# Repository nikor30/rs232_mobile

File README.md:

# RS232-WLAN-Konsole

Mobiler serieller Konsolenserver auf ESP32-Basis: mit dem WLAN-Hotspot des Geräts verbinden, `http://192.168.4.1` öffnen, Terminal auf Switch, Router oder Firewall. Keine App, kein Treiber, kein USB-Seriell-Adapter — und auf Wunsch aus der Ferne über die Leitstelle.

Firmware-Stand: **v1.8.2** · Board: **Waveshare ESP32-S3-Touch-LCD-2** · Oberflächen auf Englisch, Deutsch und Portugiesisch

## Was es kann

| Wo | Was |
|---|---|
| **Am Gerät** | Touch-Display mit Portstatus, Baudrate, Auto-Baud, BREAK, Terminal und Skripten; Akku mit Ladeanzeige und Sparmodus |
| **Im Browser** | xterm.js-Terminal über den eigenen Hotspot oder das Firmennetz, ohne Installation — am Handy wie am Notebook |
| **Im Netz** | Raw-TCP und Telnet je Port (PuTTY), Bluetooth-LE-Konsole, XMODEM/YMODEM, 802.1X (PEAP, TTLS, EAP-TLS), HTTPS |
| **Auf der SD-Karte** | Mitschnitte je Port, gespeicherte Konfigurationen zum Abspielen, verschlüsselte Sicherung; die Karte lässt sich als USB-Stick verleihen |
| **Aus der Ferne** | Leitstelle mit Geräteübersicht, Fernkonsole Ende-zu-Ende verschlüsselt, Firmware-Updates nur signiert (ML-DSA-65), Images auf die SD-Karte |

<table>
  <tr>
    <td align="center" width="38%"><br><sub>Touch-Display am Gerät</sub></td>
    <td align="center"><br><sub>Weboberfläche des Geräts am Handy</sub></td>
  </tr>
</table>

## Leitstelle

Geräte melden sich ausgehend per HTTPS bei einem Server — kein offener Port am Gerät, kein VPN. Der Kanal darin ist hybrid verschlüsselt (X25519 + ML-KEM-768); angemeldet wird mit einem sechsstelligen Code vom Display. Konten mit Passwort und Authenticator-App, Gruppen mit Rechten, Standorte, eine Bibliothek für Vorlagen, Firmware und Images.

Die **Fernkonsole** braucht einen Tipp am Gerät (oder eine dort gesetzte Frist für unbeaufsichtigten Zugriff), läuft höchstens 60 Minuten und ist Ende-zu-Ende verschlüsselt: Der Server trägt nur Chiffretext, Display und Browser zeigen denselben Code. Skripte lassen sich im Terminal abspielen, Sitzungen in eine Textdatei aufzeichnen.

## Hardware (Entwurf)

Eine Trägerplatine für das Waveshare-Modul mit **vier galvanisch getrennten RS232-Ports auf RJ45** (Cisco-Belegung; je Port Optokoppler, MAX3232E und eigener isolierter Wandler, aus dem Akku schaltbar) und ein druckbares Gehäuse. Entworfen und per KiCad-DRC geprüft, **noch nicht gebaut** — Quellen, Gerber für PCBWay und STL-Dateien im Zweig [`hardware-carrier`](../../tree/hardware-carrier/hardware).

<table>
  <tr>
    <td align="center"><br><sub>Trägerplatine 78 × 107 mm</sub></td>
    <td align="center"><br><sub>Körper, Platine, Boden</sub></td>
  </tr>
</table>

Heute läuft das Gerät mit einem MAX3232-Modul an einem Port, geprüft an Cisco C3750-X und C2960CX.

## Aufbau

- [`HANDOVER.md`](HANDOVER.md) — Projektstand, Erfahrungswissen, offene Punkte
- [`firmware/`](firmware/) — PlatformIO-Projekt für das Waveshare ESP32-S3-Touch-LCD-2 ([Weboberfläche und Netz](firmware/README.md), [Board](firmware/WAVESHARE.md))
- [`server/`](server/) — Leitstelle (Command-and-Control-Server) in Go: [Konzept](server/KONZEPT.md), [Betrieb und Admin-API](server/README.md)
- [`tests/`](tests/) — Host-Unittests der Firmware und Protokolltests gegen den Server

```bash
cd firmware
pio run -t upload                          # Englisch
pio run -e waveshare-s3-lcd2-de -t upload  # Deutsch (-pt: Portugiesisch)

cd server
docker compose up -d --build               # Leitstelle lokal, siehe server/README.md
```

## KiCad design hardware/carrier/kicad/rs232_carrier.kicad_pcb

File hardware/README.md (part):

# Hardware: Trägerplatine mit vier galvanisch getrennten RS232-Ports und Gehäuse

Stand 15. November 2026: Platine **Revision 0.4** (Neuanfang auf Grundlage des 3D-Modells des Herstellers),
Gehäuse **Revision 0.5** (neu aufgebaut nach dem ersten Probedruck).
Entworfen, geroutet, KiCad-DRC ohne elektrische Fehler, Gehäuse rechnerisch gegen das Herstellermodell
geprüft — **Platine nicht gebaut, Gehäuse in dieser Fassung nicht gedruckt.** Vor der Bestellung die Liste
„Vor der Bestellung prüfen“ abarbeiten.

> **Revision 0.3.1 und älter nicht bauen.** Dort waren die beiden Buchsenleisten für das Modul spiegelverkehrt
> belegt: Die Pinbelegung stammte aus einem Foto der Modulrückseite und wurde wie eine Ansicht von oben
> eingetragen. Jedes Signal lag am falschen Pin, VBAT und Masse eingeschlossen. Revision 0.4 nimmt die Lage
> der Stifte aus dem 3D-Modell des Herstellers, und `generate.py` prüft sie bei jedem Lauf dagegen (`HEADER`).

## Was neu ist in Revision 0.4

- **Modul exakt vermessen**: Alle Maße kommen aus dem STEP-Modell von Waveshare (Abschnitt „Das Modul“).
- **Buchsenleisten richtig herum**, Pin 1 liegt 7,60 mm vom antennenseitigen Platinenrand (vorher 7,3 mm geschätzt).
- **TX/RX per Software kreuzen**: Die Lötbrücken sind entfallen. Je Port schalten zwei Halbleiterrelais
  (CPC2330N) die beiden Leitungen an der Buchse um; die Firmware steuert das über GPIO2/4/6/7.
- **Prüfung der Schaltung, Korrekturen**: isolierter Wandler mit 3,3 V statt 5 V Ausgang (der B0505S liefert
  im Leerlauf über 5,5 V, mehr als der MAX3232 verträgt), Ladungspumpen-Kondensatoren 470 nF, Teiler des
  Aufwärtswandlers 270k/36k, BSS138 statt 2N7002 (schaltet mit 3,3 V sicher), TVS-Dioden an jeder Buchse,
  Verpolschutz am Akkuanschluss, zweiter Akkustecker (MX1.25 wie am Modul).
- **Gehäuse neu in echtem CAD** (CadQuery/OpenCascade, STEP und STL), seit dem ersten Probedruck in
  Revision 0.5: Das Displayglas liegt bündig in einer Öffnung der Oberseite auf einem eigenen Rahmen, in dem
  das Modul geklemmt ist; der Boden rastet mit vier Federarmen; am USB-C-Ende **zwei Tasten für RST und
  BOOT, mitgedruckt als Federzungen des Rahmens**. Drei Teile, nichts Loses, kein Teil braucht Stützen. Das alte OpenSCAD-Gehäuse ist entfernt (es war zusätzlich seitenverkehrt).

## Das Modul

Waveshare ESP32-S3-Touch-LCD-2. Der Hersteller stellt ein vollständiges 3D-Modell bereit
(`esp32-s3-touch-lcd-2_20241108.stp`, STEP AP203 aus Creo, 314 Körper, von CATIA V5 und 3DEXPERIENCE direkt
lesbar), dazu Maßzeichnung und Schaltplan. Die Dateien liegen **nicht im Repository** (Herkunft und Lizenz
beim Hersteller); `vendor/README.md` nennt die Adressen. `enclosure/case.py` prüft das Gehäuse gegen dieses
Modell, wenn es in `hardware/vendor/` liegt.

Koordinaten des Herstellermodells: x quer, y längs (USB-C bei −y, Antenne bei +y), z nach oben zur
Displayseite; Glasoberseite z = +3,60, Platine z = −3,60 … −2,00.

| Maß | Wert (mm) |
|---|---|
| Deckglas | 37,10 × 58,80 × 1,10, Ecken R 2,60 |
| Platine | 35,02 × 48,22 × 1,60 |
| Glasüberstand über die Platine | 5,08 an der USB-C-Seite, 5,50 an der Antennenseite, 1,04 je Längsseite |
| Stapel | Glas 1,10, Touchfolie 0,40, LCD 2,10, Acrylplatte 2,00, Platine 1,60 |
| Glasoberseite bis Platinenunterseite | 7,20 |
| Glasoberseite bis Unterkante der Stiftleistenkörper | 9,70 |
| Glasoberseite bis Stiftspitzen | 15,50 |
| Stiftleisten | 2 × 14 Stifte, Raster 2,54, Reihen 30,48 auseinander; Pin 1 und Pin 28 an der Antennenseite, 7,60 vom Platinenrand |
| Abstandsbolzen M2 | vier, 29,00 × 42,20 |
| Sichtfläche des Displays | 30,99 × 41,20 (240 × 320 Bildpunkte) |
| USB-C-Buchse | Schale außen 8,94 × 3,16, Öffnung 8,34 × 2,56, Achse 1,67 unter der Platinenunterseite, Vorderkante 1,18 über dem Platinenrand und 3,90 hinter der Glaskante; ein Steckerblech taucht 4,78 ein |
| Taster RST und BOOT | TS24CA, seitlich betätigt, Gehäuse 4,55 × 2,30 × 1,80; Stößel 2,00 × 1,00, 1,20 vor dem Tastergehäuse, Spitze 0,28 hinter dem Platinenrand, Achse 0,90 unter der Platinenunterseite; Stößel 18,92 auseinander (RST bei x = +9,47, BOOT bei x = −9,45) |

Das Maßblatt `enclosure/out/waveshare_module_dimensions.pdf` zeigt alles in drei Ansichten. Alle Zahlen stehen
in `carrier/generate.py` im Wörterbuch `WS`; Platine und Gehäuse lesen sie von dort.

Aus dem Schaltplan des Herstellers: Stift 14 (VBAT) ist das Akkunetz des Laders, am MX1.25-Stecker ist Pin 1
der Pluspol, der Stift „5V“ ist USB-VBUS. **Das Modul hat nur eine Keramikantenne und keine IPEX-Buchse**;
eine externe Antenne ginge nur mit Umbau am Modul. Das Gehäuse hat deshalb keine SMA-Bohrung mehr.

## Verzeichnis

| Pfad | Inhalt |
|---|---|
| `carrier/generate.py` | **Die Quelle.** Maße des Moduls (`WS`), Schaltplan, Platine, DRC-Regeln, `bom.csv`, `preview.png` |
| `carrier/kigen.py` | Schreiber für KiCad-7-Dateien (Symbole und Footprints eingebettet, auch für die Unterseite) |
| `carrier/route.py` | Eigener Gitter-Autorouter (zwei Lagen, Vias, Bauteile auf beiden Seiten, Masseflächen) |
| `carrier/drc.py` | Zonen füllen, KiCad-DRC, Fertigungsdaten nach `kicad/fab/` |
| `carrier/check_pours.py` | Prüft unabhängig vom DRC, dass jede Massefläche zusammenhängt, und nennt den Ort einer abgetrennten Insel |
| `carrier/kicad/` | KiCad-7-Projekt; `channel.kicad_sch` ist ein Port und viermal eingebunden |
| `carrier/kicad/fab/` | **Gerber und Bohrdaten als ZIP**, Bestückungsdaten, Schaltplan- und Platinen-PDF, DRC-Bericht |
| `enclosure/case.py` | Gehäuse: Körper, Rahmen (mit den beiden Tasten), Boden; STEP, STL, Prüfungen. Braucht CadQuery |
| `enclosure/printcheck.py` | Prüft die druckfertigen Dateien: Was beginnt über dem Bett in der Luft, und was hält es |
| `enclosure/render.py` | Bilder (POV-Ray) und die Schnittzeichnung `out/detail_sections.png` |
| `enclosure/module_sheet.py` | Maßblatt des Moduls |
| `enclosure/out/` | `body`, `frame`, `base` als STEP und STL, `print/` mit den Teilen in Drucklage, `rs232_console_assembly.step`, Bilder |
| `vendor/` | Hinweis, woher das Herstellermodell kommt (die Dateien selbst nicht) |
| `hat/` | **Zwei-Port-Prototyp** „RS232 CONSOLE HAT v3.0“: Fertigungsdaten, `board.py`, Beschreibung des Gehäuses dazu (`hat/README.md`) |
| `enclosure/out_hat/` | Gehäuse für den Zwei-Port-Prototyp (`case.py --hat`): dieselben Dateien |

Neu erzeugen (KiCad 7, POV-Ray und `pip install cadquery`):

```bash
cd hardware/carrier && python3 generate.py && python3 route.py && python3 drc.py && python3 check_pours.py
cd ../enclosure && python3 case.py && python3 render.py && python3 module_sheet.py
```

`generate.py` ist deterministisch. Änderungen gehören dorthin, nicht in die KiCad-Dateien. Immer in dieser
Reihenfolge laufen lassen und nie zwei Läufe zugleich: `route.py` hängt seine Bahnen an die Platinendatei an.

Der Router ist seit diesem Stand wiederholbar (gleiche Eingabe, gleiches Ergebnis). Drei Masseanschlüsse
bekommen keine eigene Bahn und hängen nur an der Massefläche (`route.py` meldet „left to the pour“). Ob die
Fläche sie wirklich erreicht, entscheidet erst die Füllung in KiCad; `drc.py` und `check_pours.py` prüfen das.
Meldet eines der beiden nach einer Änderung an der Platzierung eine offene Verbindung, hilft ein anderer
Startwert: `ROUTE_SEED=2 python3 route.py`.

## Pinbelegung am Modul

| Port | RX (ESP-Eingang) | TX (ESP-Ausgang) | Versorgung an | Kreuzen |
|---|---|---|---|---|
| 1 | GPIO44 | GPIO21 | GPIO16 | GPIO2 |
| 2 | GPIO15 | GPIO13 | GPIO17 | GPIO4 |
| 3 | GPIO11 | GPIO12 | GPIO18 | GPIO6 |
| 4 | GPIO14 | GPIO9 | GPIO10 | GPIO7 |

GPIO2/4/6/7 gehören am Modul zum Kamerastecker und sind ohne Kamera frei. GPIO43 (U0TXD) bleibt frei, weil
das ROM beim Reset dort schreibt; er liegt mit 3V3, Masse, I²C (GPIO47/48), GPIO8 und VBUS an Stecker J3.
Das Häkchen „RX/TX am Pegelwandler tauschen“ der Firmware darf mit dieser Platine nicht gesetzt werden
(die Optokoppler haben eine feste Richtung).

## Signalweg eines Ports

```
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
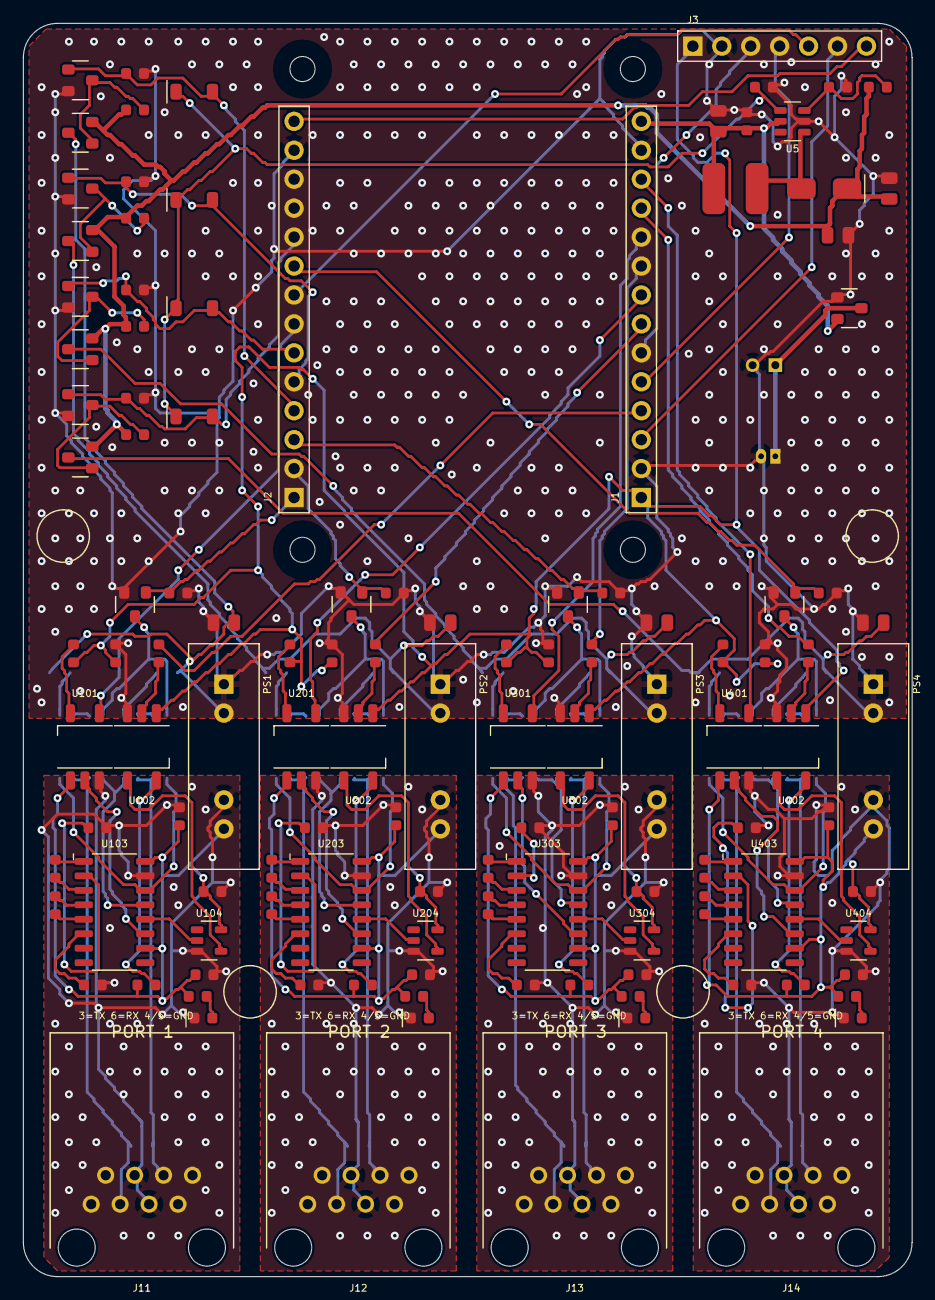
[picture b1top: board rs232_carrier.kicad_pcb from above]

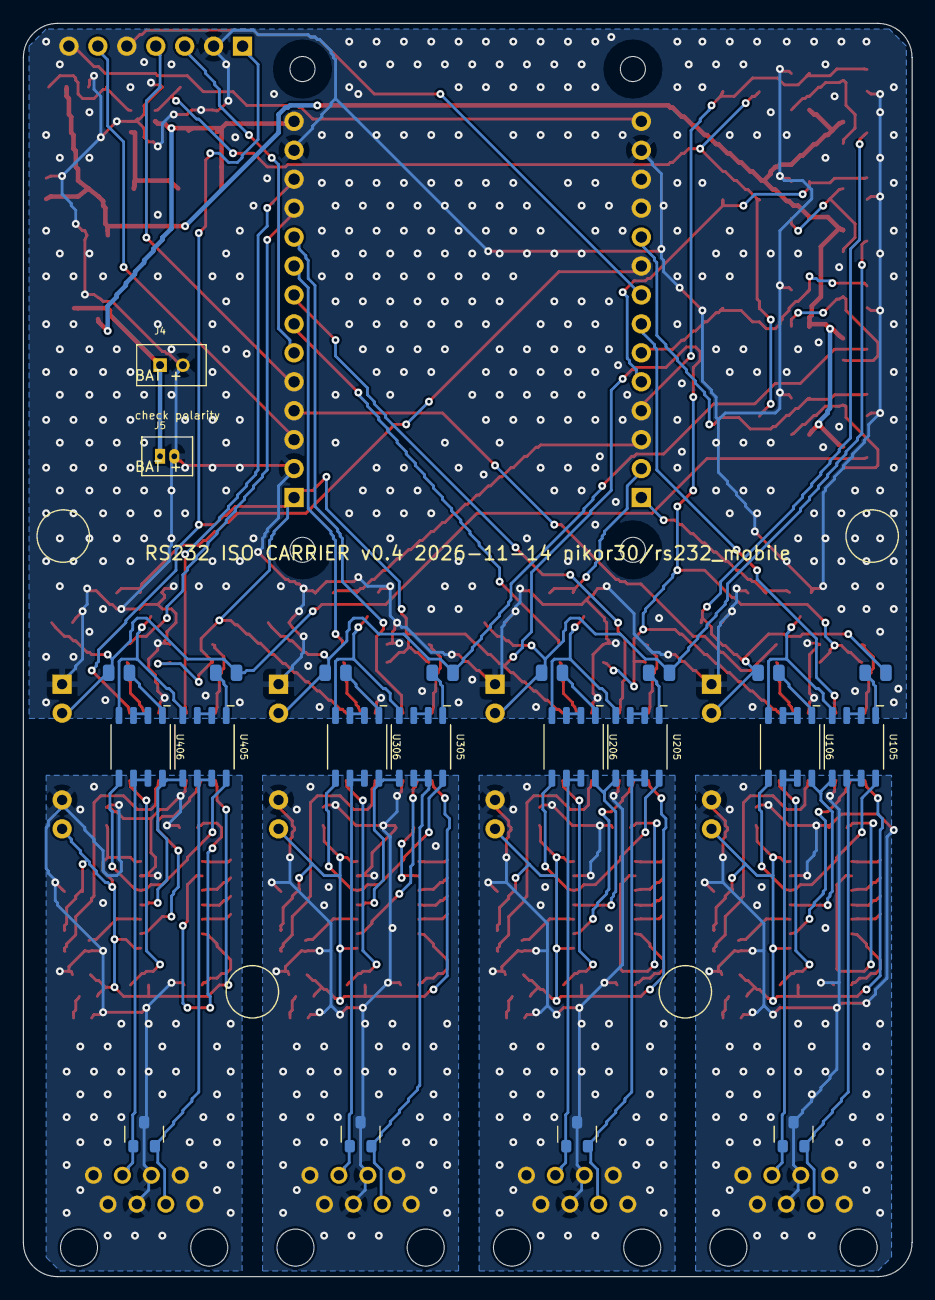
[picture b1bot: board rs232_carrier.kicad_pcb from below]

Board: 2 copper layers, 78.0 x 110.0 mm, 148 parts (22 on the bottom side), 133 nets.

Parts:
C51: 10u; C_0805
C52, C53: 22u; C_0805
C54, C101, C105, C107, C108, C201, C205, C207, C208, C301, C305, C307, C308, C401, C405, C407, C408: 100n; C_0603
C102, C103, C104, C202, C203, C204, C302, C303, C304, C402, C403, C404: 470n; C_0603
C109, C209, C309, C409: 4.7u; C_0603
C110, C210, C310, C410: 2.2u; C_0805
D5: SS14; D_SMA
D51, D52, D53, D54: 1N4148W; D_SOD-123
D101, D201, D301, D401: LED green; LED_0603
D102, D202, D302, D402: PESD15VL2BT; SOT-23
H1, H2, H3, H4: M2 Waveshare; MountingHole_2.2
J1: WS header 1-14; PinSocket_1x14
J2: WS header 15-28; PinSocket_1x14_B
J3: EXT; PinHeader_1x7
J4: BAT JST-PH; JST_PH_2_Vertical
J5: BAT MX1.25; MX125_2_Vertical
J11, J12, J13, J14: RJ45; RJ45_Generic
L1: 22u; L_5x5
PS1, PS2, PS3, PS4: B0503S-1WR3; SIP-4_DCDC
Q5, Q12, Q22, Q32, Q42: AO3401A; SOT-23
Q11, Q21, Q31, Q41, Q101, Q201, Q301, Q401: BSS138; SOT-23
R51: 270k; R_0603
R52: 36k; R_0603
R53, R61, R62, R63, R64, R71, R72, R73, R74, R107, R207, R307, R407: 100k; R_0603
R101, R102, R201, R202, R301, R302, R401, R402: 330; R_0603
R103, R203, R303, R403: 100; R_0603
R104, R204, R304, R404: 1k; R_0603
R105, R106, R205, R206, R305, R306, R405, R406: 470; R_0805
U5: MT3608; SOT-23-6
U101, U102, U201, U202, U301, U302, U401, U402: TLP2361; SO6_Opto
U103, U203, U303, U403: MAX3232E; SOIC-16
U104, U204, U304, U404: 74LVC1G17; SOT-23-5
U105, U106, U205, U206, U305, U306, U405, U406: CPC2330N; SOIC-8

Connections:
+3V3: C107.1, C207.1, C307.1, C407.1, J1.1, J3.1, R101.1, R201.1, R301.1, R401.1, U102.6, U202.6, U302.6, U402.6
+5V: C52.1, C53.1, D5.1, Q12.2, Q22.2, Q32.2, Q42.2, R51.1, R71.1, R72.1, R73.1, R74.1
/CH1/BUF_OUT: U102.3, U104.4
/CH1/C1N: C101.2, U103.3
/CH1/C1P: C101.1, U103.1
/CH1/C2N: C102.2, U103.5
/CH1/C2P: C102.1, U103.4
/CH1/ISOGND: C103.2, C104.2, C105.2, C108.2, C109.2, D101.1, D102.3, J11.4, J11.5, PS1.3, U101.4, U103.15, U104.3
/CH1/LEDA: D101.2, R104.2
/CH1/R1IN: U103.13, U105.5, U106.8
/CH1/R1OUT: U103.12, U104.2
/CH1/RJ3: D102.1, J11.3, U106.6, U106.7
/CH1/RJ6: D102.2, J11.6, U105.6, U105.7
/CH1/RXA: R102.2, U102.1
/CH1/RX_O: R103.1, U102.5
/CH1/SWA1: R105.2, U105.1
/CH1/SWA2: U105.2, U105.3
/CH1/SWB1: R106.2, U106.1
/CH1/SWB2: U106.2, U106.3
/CH1/SWK: Q101.3, U105.4, U106.4
/CH1/T1IN: U101.5, U103.11
/CH1/T1OUT: U103.14, U105.8, U106.5
/CH1/TXA: R101.2, U101.1
/CH1/VISO: C105.1, C108.1, C109.1, PS1.4, R102.1, R104.1, U101.6, U103.10, U103.16, U104.5
/CH1/VN: C104.1, U103.6
/CH1/VP: C103.1, U103.2
/CH2/BUF_OUT: U202.3, U204.4
/CH2/C1N: C201.2, U203.3
/CH2/C1P: C201.1, U203.1
/CH2/C2N: C202.2, U203.5
/CH2/C2P: C202.1, U203.4
/CH2/ISOGND: C203.2, C204.2, C205.2, C208.2, C209.2, D201.1, D202.3, J12.4, J12.5, PS2.3, U201.4, U203.15, U204.3
/CH2/LEDA: D201.2, R204.2
/CH2/R1IN: U203.13, U205.5, U206.8
/CH2/R1OUT: U203.12, U204.2
/CH2/RJ3: D202.1, J12.3, U206.6, U206.7
/CH2/RJ6: D202.2, J12.6, U205.6, U205.7
/CH2/RXA: R202.2, U202.1
/CH2/RX_O: R203.1, U202.5
/CH2/SWA1: R205.2, U205.1
/CH2/SWA2: U205.2, U205.3
/CH2/SWB1: R206.2, U206.1
/CH2/SWB2: U206.2, U206.3
/CH2/SWK: Q201.3, U205.4, U206.4
/CH2/T1IN: U201.5, U203.11
/CH2/T1OUT: U203.14, U205.8, U206.5
/CH2/TXA: R201.2, U201.1
/CH2/VISO: C205.1, C208.1, C209.1, PS2.4, R202.1, R204.1, U201.6, U203.10, U203.16, U204.5
/CH2/VN: C204.1, U203.6
/CH2/VP: C203.1, U203.2
/CH3/BUF_OUT: U302.3, U304.4
/CH3/C1N: C301.2, U303.3
/CH3/C1P: C301.1, U303.1
/CH3/C2N: C302.2, U303.5
/CH3/C2P: C302.1, U303.4
/CH3/ISOGND: C303.2, C304.2, C305.2, C308.2, C309.2, D301.1, D302.3, J13.4, J13.5, PS3.3, U301.4, U303.15, U304.3
/CH3/LEDA: D301.2, R304.2
/CH3/R1IN: U303.13, U305.5, U306.8
/CH3/R1OUT: U303.12, U304.2
/CH3/RJ3: D302.1, J13.3, U306.6, U306.7
/CH3/RJ6: D302.2, J13.6, U305.6, U305.7
/CH3/RXA: R302.2, U302.1
/CH3/RX_O: R303.1, U302.5
/CH3/SWA1: R305.2, U305.1
/CH3/SWA2: U305.2, U305.3
/CH3/SWB1: R306.2, U306.1
/CH3/SWB2: U306.2, U306.3
/CH3/SWK: Q301.3, U305.4, U306.4
/CH3/T1IN: U301.5, U303.11
/CH3/T1OUT: U303.14, U305.8, U306.5
/CH3/TXA: R301.2, U301.1
/CH3/VISO: C305.1, C308.1, C309.1, PS3.4, R302.1, R304.1, U301.6, U303.10, U303.16, U304.5
/CH3/VN: C304.1, U303.6
/CH3/VP: C303.1, U303.2
/CH4/BUF_OUT: U402.3, U404.4
/CH4/C1N: C401.2, U403.3
/CH4/C1P: C401.1, U403.1
/CH4/C2N: C402.2, U403.5
/CH4/C2P: C402.1, U403.4
/CH4/ISOGND: C403.2, C404.2, C405.2, C408.2, C409.2, D401.1, D402.3, J14.4, J14.5, PS4.3, U401.4, U403.15, U404.3
/CH4/LEDA: D401.2, R404.2
/CH4/R1IN: U403.13, U405.5, U406.8
/CH4/R1OUT: U403.12, U404.2
/CH4/RJ3: D402.1, J14.3, U406.6, U406.7
/CH4/RJ6: D402.2, J14.6, U405.6, U405.7
/CH4/RXA: R402.2, U402.1
/CH4/RX_O: R403.1, U402.5
/CH4/SWA1: R405.2, U405.1
/CH4/SWA2: U405.2, U405.3
/CH4/SWB1: R406.2, U406.1
/CH4/SWB2: U406.2, U406.3
/CH4/SWK: Q401.3, U405.4, U406.4
/CH4/T1IN: U401.5, U403.11
/CH4/T1OUT: U403.14, U405.8, U406.5
/CH4/TXA: R401.2, U401.1
/CH4/VISO: C405.1, C408.1, C409.1, PS4.4, R402.1, R404.1, U401.6, U403.10, U403.16, U404.5
/CH4/VN: C404.1, U403.6
/CH4/VP: C403.1, U403.2
BATP: J4.1, J5.1, Q5.3
EN1: D51.2, J2.25, Q11.1, R61.1
EN2: D52.2, J2.24, Q21.1, R62.1
EN3: D53.2, J2.23, Q31.1, R63.1
EN4: D54.2, J2.19, Q41.1, R64.1
ESP_RX1: J1.4, R103.2
ESP_RX2: J1.7, R203.2
ESP_RX3: J1.9, R303.2
ESP_RX4: J1.11, R403.2
ESP_TX1: J2.22, U101.3
ESP_TX2: J1.8, U201.3
ESP_TX3: J1.10, U301.3
ESP_TX4: J1.12, U401.3
FB: R51.2, R52.1, U5.3
GND: C51.2, C52.2, C53.2, C54.2, C107.2, C110.2, C207.2, C210.2, C307.2, C310.2, C407.2, C410.2, J1.2, J1.13, J2.16, J3.2, J4.2, J5.2, PS1.1, PS2.1, PS3.1, PS4.1, Q5.1, Q11.2, Q21.2, Q31.2, Q41.2, Q101.2, Q201.2, Q301.2, Q401.2, R52.2, R53.2, R61.2, R62.2, R63.2, R64.2, R107.2, R207.2, R307.2, R407.2, U5.2, U102.4, U202.4, U302.4, U402.4
IO8: J2.21, J3.5
ISO_IN1: C110.1, PS1.2, Q12.3, R105.1, R106.1
ISO_IN2: C210.1, PS2.2, Q22.3, R205.1, R206.1
ISO_IN3: C310.1, PS3.2, Q32.3, R305.1, R306.1
ISO_IN4: C410.1, PS4.2, Q42.3, R405.1, R406.1
PG1: Q11.3, Q12.1, R71.2
PG2: Q21.3, Q22.1, R72.2
PG3: Q31.3, Q32.1, R73.2
PG4: Q41.3, Q42.1, R74.2
PWR_EN: D51.1, D52.1, D53.1, D54.1, R53.1, U5.4
SCL: J1.5, J3.4
SDA: J1.6, J3.3
SW: D5.2, L1.2, U5.1
SWAP1: J2.28, Q101.1, R107.1
SWAP2: J2.27, Q201.1, R207.1
SWAP3: J2.26, Q301.1, R307.1
SWAP4: J2.20, Q401.1, R407.1
TXD0: J1.3, J3.6
VBAT: C51.1, C54.1, J1.14, L1.1, Q5.2, U5.5
VBUS: J2.15, J3.7

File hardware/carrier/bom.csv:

refs,qty,value,footprint,suggested part,note
C54 C101 C105 C107 C108 C201 C205 C207 C208 C301 C305 C307 C308 C401 C405 C407 C408,17,100n,C_0603,100n 0603 X7R/X5R >=10 V,ceramic
C109 C209 C309 C409,4,4.7u,C_0603,4.7u 0603 X7R/X5R >=10 V,ceramic
C102 C103 C104 C202 C203 C204 C302 C303 C304 C402 C403 C404,12,470n,C_0603,470n 0603 X7R/X5R >=10 V,ceramic
C51,1,10u,C_0805,10u 0805 X7R/X5R >=10 V,ceramic
C110 C210 C310 C410,4,2.2u,C_0805,2.2u 0805 X7R/X5R >=10 V,ceramic
C52 C53,2,22u,C_0805,22u 0805 X7R/X5R >=10 V,ceramic
D5,1,SS14,D_SMA,Vishay SS14,"40 V Schottky, SMA"
D51 D52 D53 D54,4,1N4148W,D_SOD-123,Diodes Inc 1N4148W-7-F,
J4,1,BAT JST-PH,JST_PH_2_Vertical,JST B2B-PH-K-S,"2 mm battery plug, bottom side; fit this OR the 1.25 mm header"
D101 D201 D301 D401,4,LED green,LED_0603,Everlight 19-217/GHC-YR1S2/3T,"any 0603 green LED, cathode mark"
L1,1,22u,L_5x5,Bourns SRN5040-220M,"22 uH, >=1 A sat; any 4x4..5x5 mm shielded inductor with 2 pads"
J5,1,BAT MX1.25,MX125_2_Vertical,Molex 53047-0210,"1.25 mm battery plug as on the Waveshare module, bottom side"
J3,1,EXT,PinHeader_1x7,1x7 pin header 2.54 mm,optional
J1,1,WS header 1-14,PinSocket_1x14,"1x14 socket 2.54 mm, 8.5 mm","female header, the Waveshare module plugs in"
J2,1,WS header 15-28,PinSocket_1x14_B,"1x14 socket 2.54 mm, 8.5 mm",female header
J11 J12 J13 J14,4,RJ45,RJ45_Generic,Amphenol 54602-908LF,"8P8C tab-down, no magnetics, no LEDs; footprint must match the chosen part"
R103 R203 R303 R403,4,100,R_0603,100 0603 1%,
R53 R61 R62 R63 R64 R71 R72 R73 R74 R107 R207 R307 R407,13,100k,R_0603,100k 0603 1%,
R104 R204 R304 R404,4,1k,R_0603,1k 0603 1%,
R51,1,270k,R_0603,270k 0603 1%,
R101 R102 R201 R202 R301 R302 R401 R402,8,330,R_0603,330 0603 1%,
R52,1,36k,R_0603,36k 0603 1%,
R105 R106 R205 R206 R305 R306 R405 R406,8,470,R_0805,470 0805 1%,
PS1 PS2 PS3 PS4,4,B0503S-1WR3,SIP-4_DCDC,Mornsun B0503S-1WR3,"5 V in, 3.3 V out, 1 W, 1.5 kV; NOT the 5 V-output B0505S. Verify pin spacing 2.54/7.62"
U101 U102 U201 U202 U301 U302 U401 U402,8,TLP2361,SO6_Opto,"Toshiba TLP2361(E,T)","alt. Broadcom ACPL-M61L-000E (same pinout); 10 Mbd, 2.7-5.5 V"
U103 U203 U303 U403,4,MAX3232E,SOIC-16,TI MAX3232ECDR,"alt. Maxim MAX3232ECSE+, Exar SP3232EEN-L; ESD-protected version"
U105 U106 U205 U206 U305 U306 U405 U406,8,CPC2330N,SOIC-8,IXYS/Littelfuse CPC2330N,"1 Form A + 1 Form B PhotoMOS, 350 V, SOIC-8; bottom side. VERIFY the pinout before ordering"
Q5 Q12 Q22 Q32 Q42,5,AO3401A,SOT-23,Alpha&Omega AO3401A,P-channel high-side switch
Q11 Q21 Q31 Q41 Q101 Q201 Q301 Q401,8,BSS138,SOT-23,onsemi BSS138,"logic-level N-MOSFET (Vth max 1.5 V), driven straight from a 3.3 V GPIO"
D102 D202 D302 D402,4,PESD15VL2BT,SOT-23,Nexperia PESD15VL2BT,two bidirectional 15 V TVS lines; protects the relay contacts and the MAX3232
U104 U204 U304 U404,4,74LVC1G17,SOT-23-5,TI SN74LVC1G17DBVR,alt. Nexperia 74LVC1G17GV; Schmitt buffer drives the RX LED
U5,1,MT3608,SOT-23-6,Aerosemi MT3608,boost VBAT -> 5.1 V; alt. TPS61023 (different footprint)

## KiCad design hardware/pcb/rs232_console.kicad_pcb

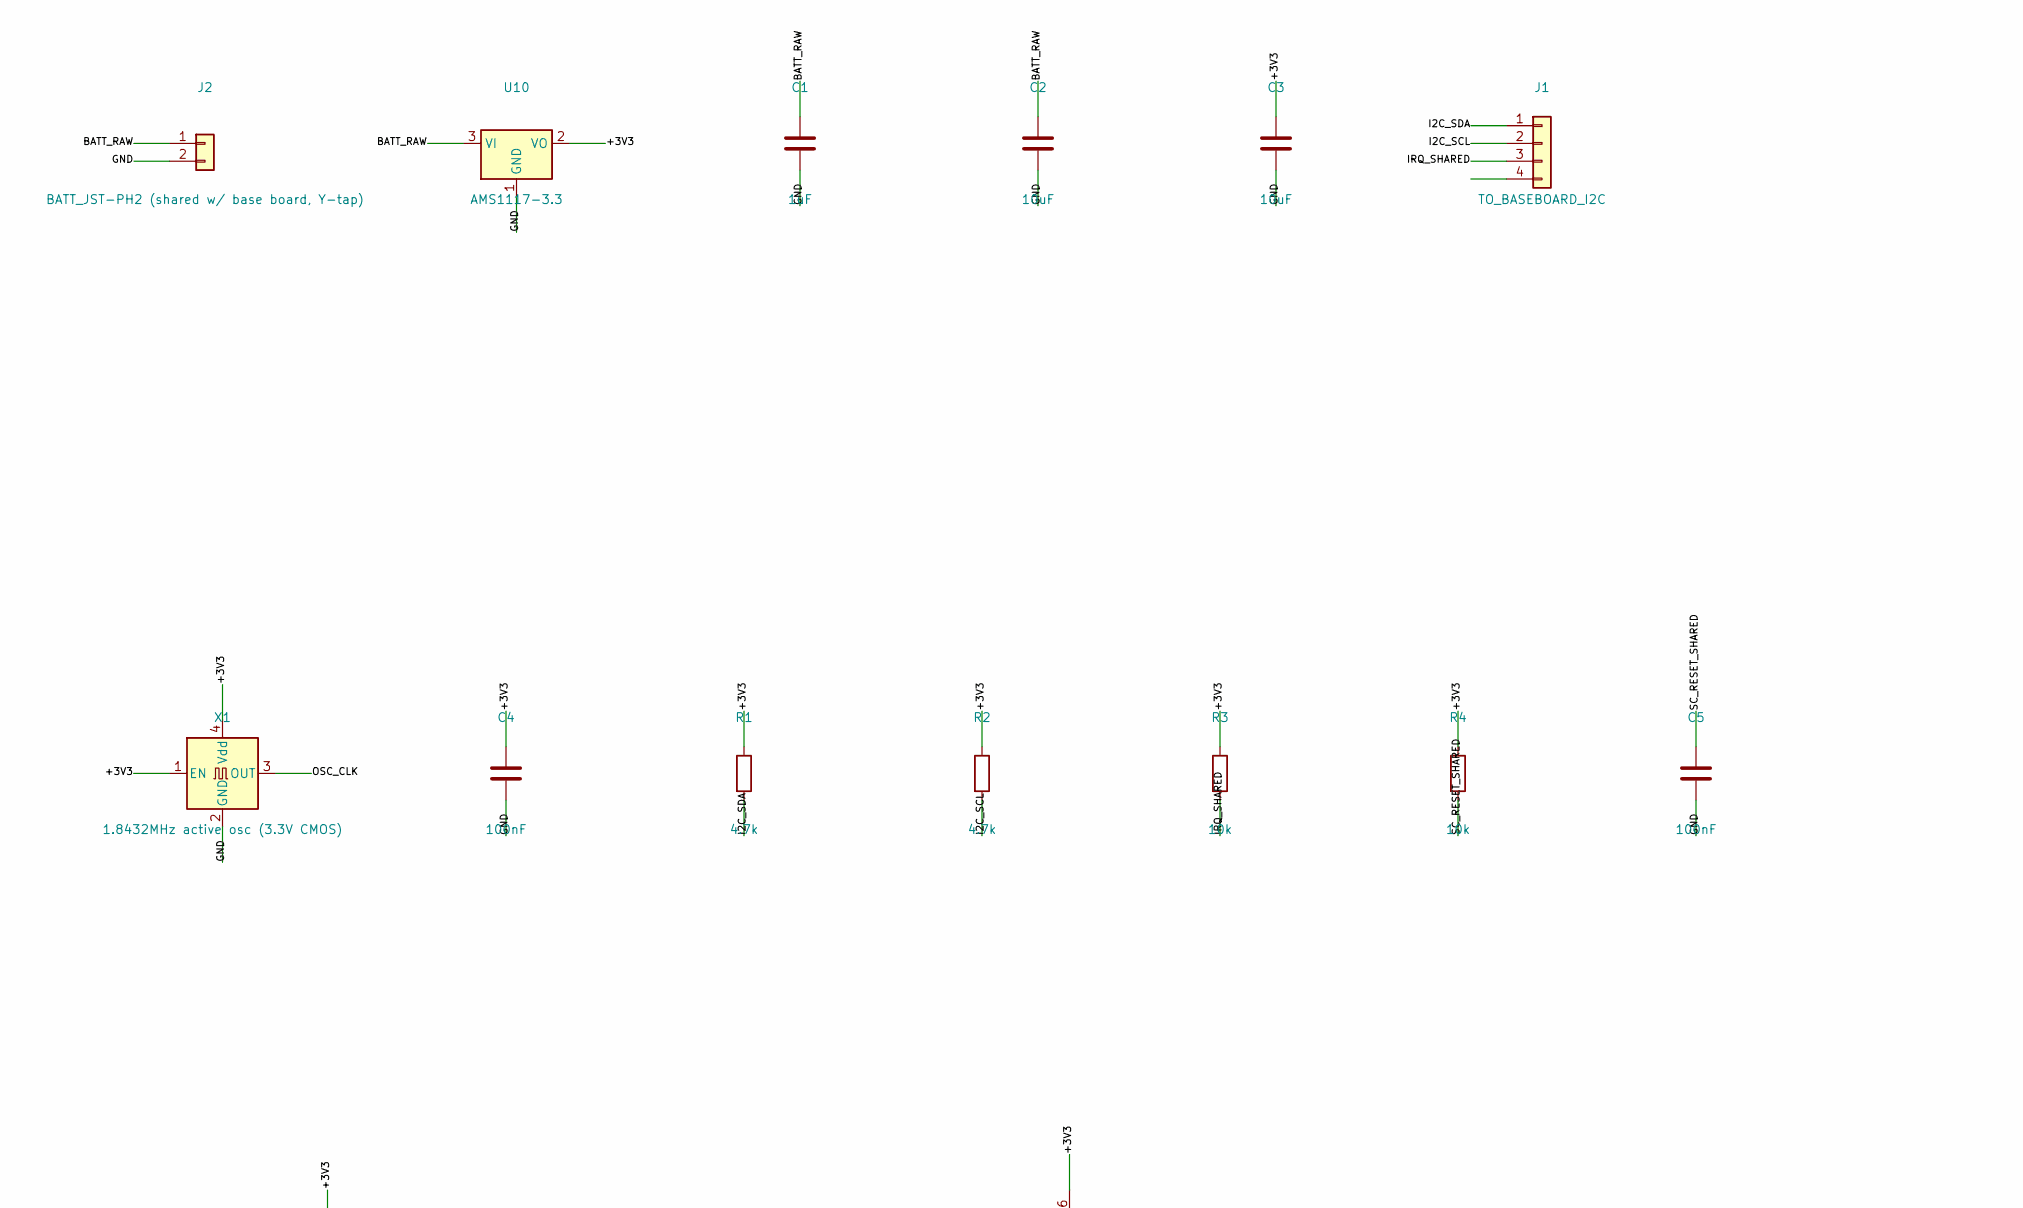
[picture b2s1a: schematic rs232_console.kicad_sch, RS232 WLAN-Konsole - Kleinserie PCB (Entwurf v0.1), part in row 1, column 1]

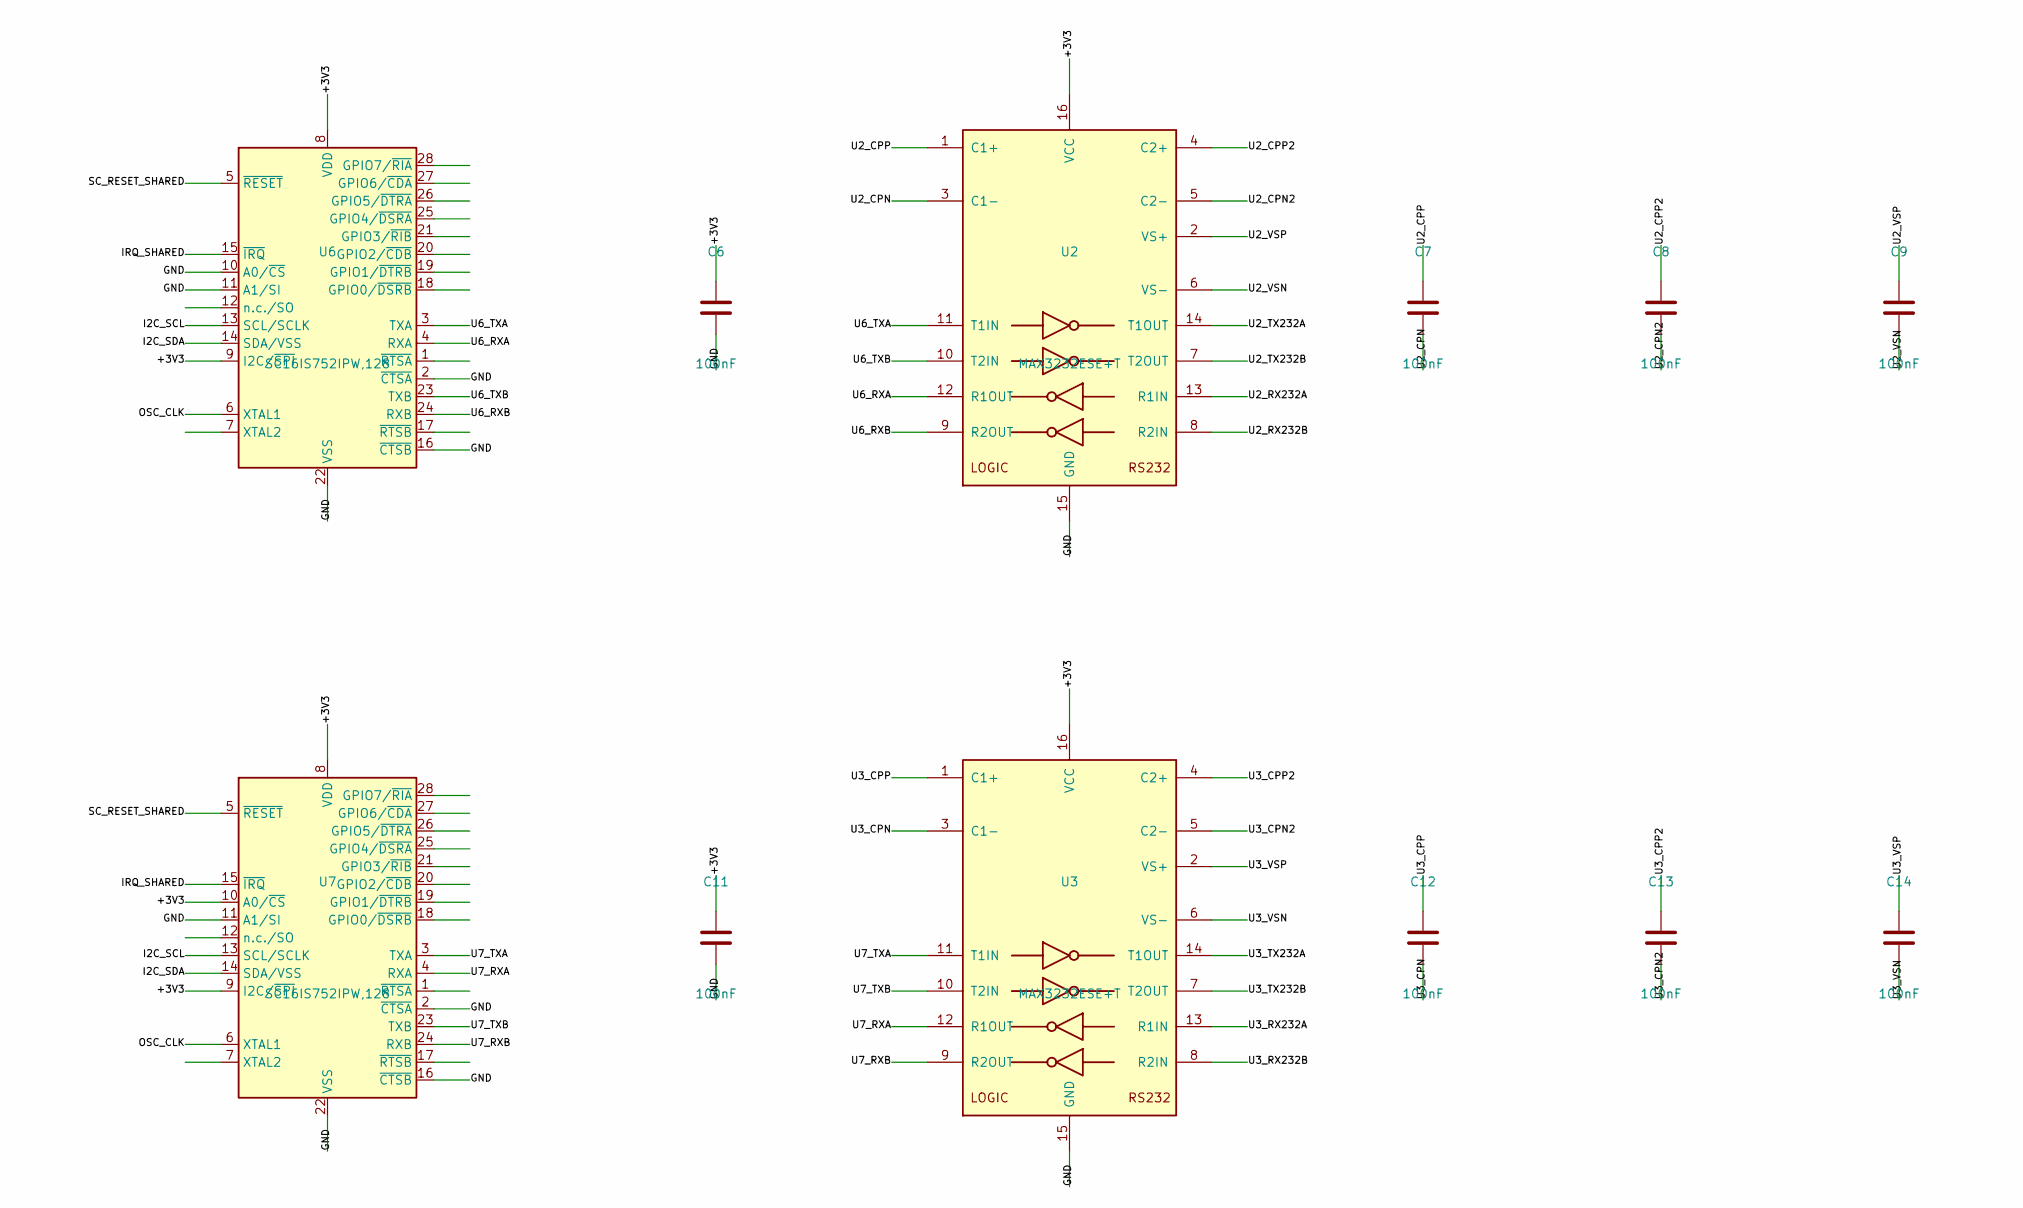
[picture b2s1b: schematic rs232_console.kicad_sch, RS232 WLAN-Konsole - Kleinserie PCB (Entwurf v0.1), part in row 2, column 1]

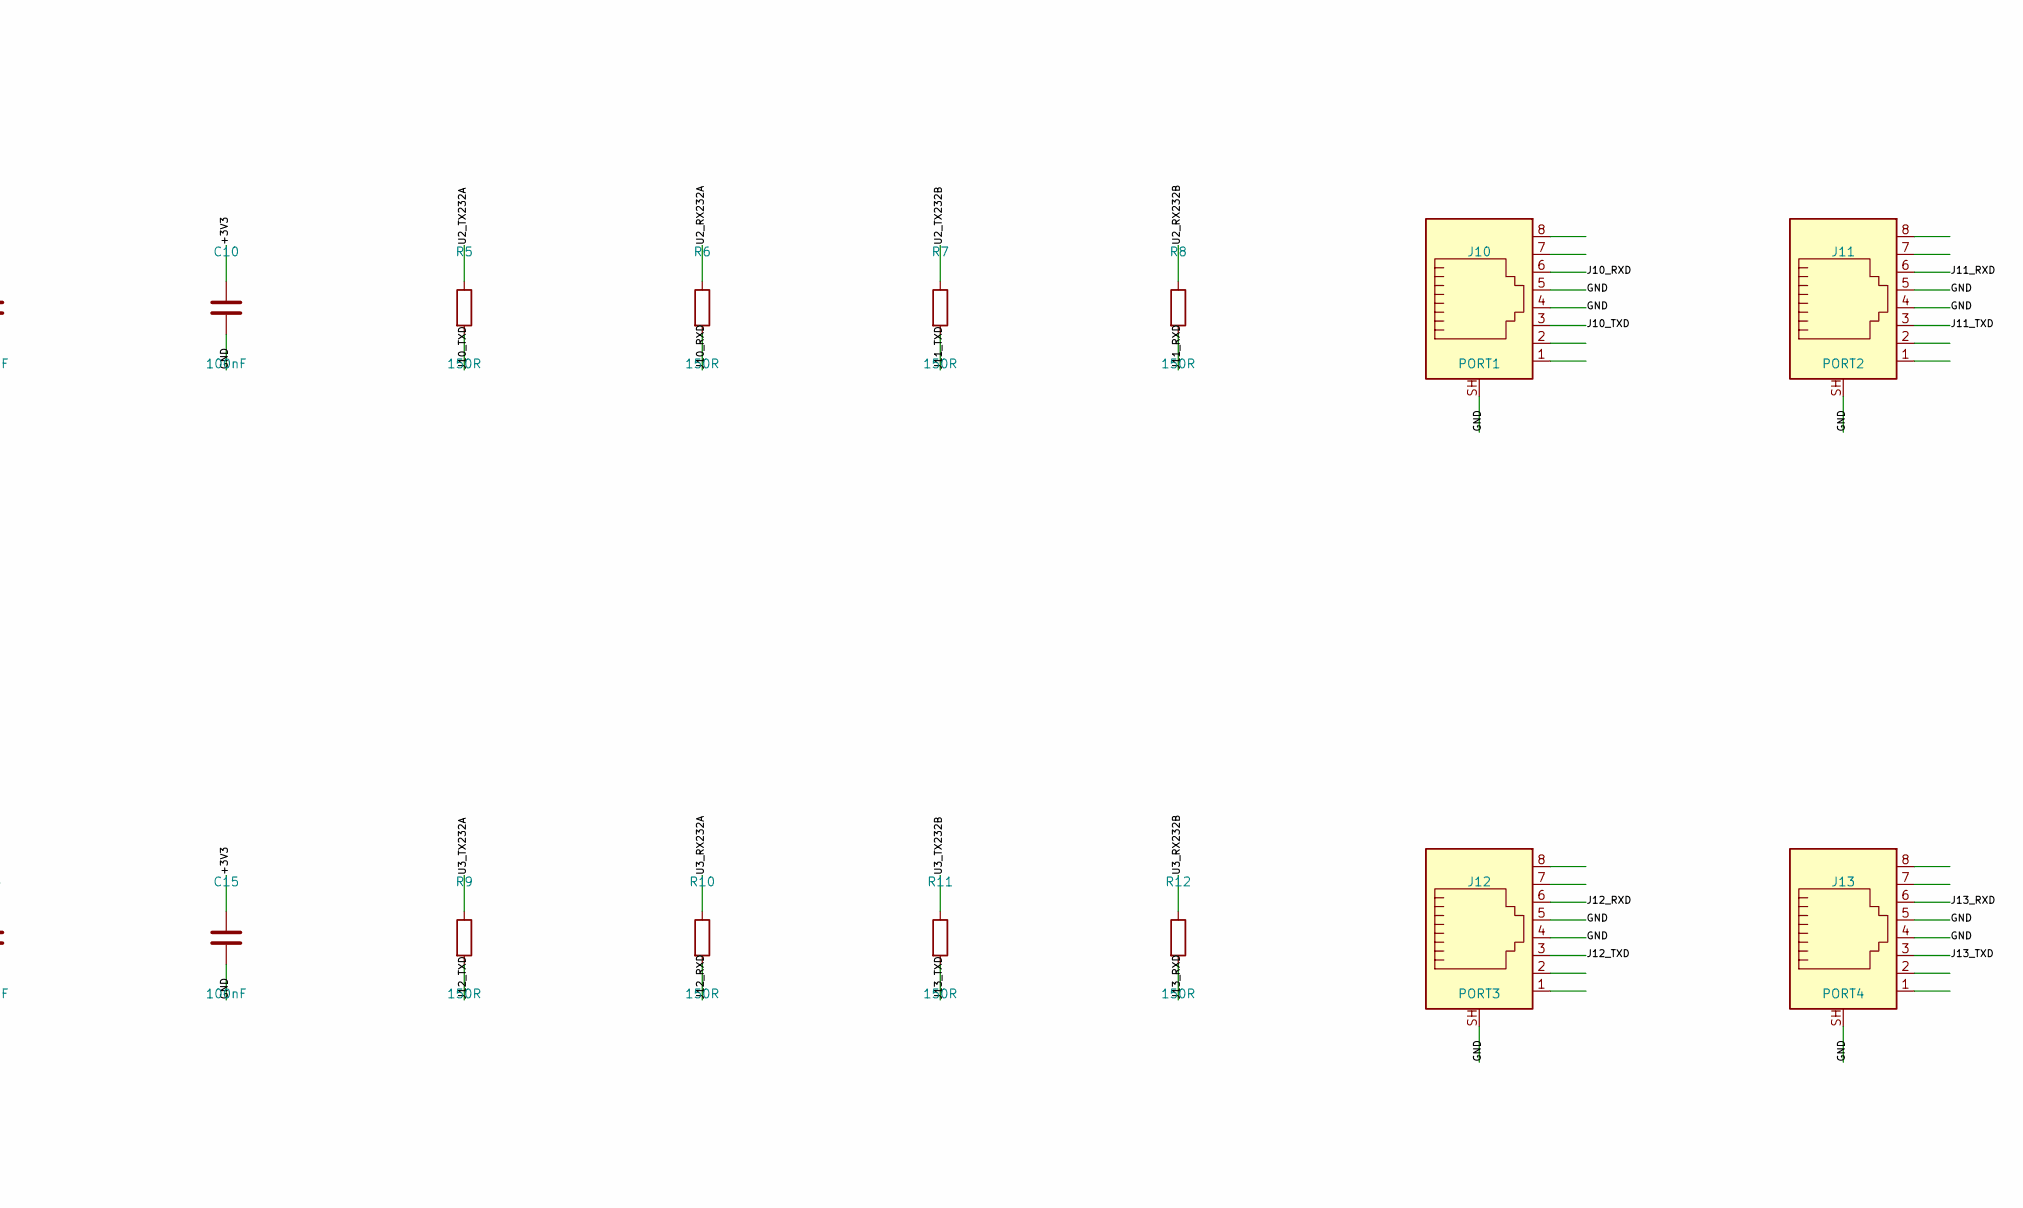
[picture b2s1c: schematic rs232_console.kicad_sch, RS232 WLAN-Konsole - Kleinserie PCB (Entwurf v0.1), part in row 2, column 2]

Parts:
C1: 1uF; C_0805_2012Metric
C2, C3: 10uF; C_0805_2012Metric
C4, C5, C6, C7, C8, C9, C10, C11, C12, C13, C14, C15: 100nF; C_0805_2012Metric
J1: TO_BASEBOARD_I2C; JST_SH_BM04B-SRSS-TB_1x04-1MP_P1.00mm_Vertical
J2: BATT_JST-PH2 (shared w/ base board, Y-tap); PinHeader_1x02_P2.54mm_Vertical
J10: PORT1; RJ45_Amphenol_RJHSE5380
J11: PORT2; RJ45_Amphenol_RJHSE5380
J12: PORT3; RJ45_Amphenol_RJHSE5380
J13: PORT4; RJ45_Amphenol_RJHSE5380
R1, R2: 4.7k; R_0805_2012Metric
R3, R4: 10k; R_0805_2012Metric
R5, R6, R7, R8, R9, R10, R11, R12: 150R; R_0805_2012Metric
U2, U3: MAX3232ESE+T; SOIC-16_3.9x9.9mm_P1.27mm
U6, U7: SC16IS752IPW,128; TSSOP-28_4.4x9.7mm_P0.65mm
U10: AMS1117-3.3; SOT-223-3_TabPin2
X1: 1.8432MHz active osc (3.3V CMOS); Oscillator_SMD_Abracon_ASE-4Pin_3.2x2.5mm

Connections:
+3V3: C3.1, C4.1, C6.1, C10.1, C11.1, C15.1, R1.1, R2.1, R3.1, R4.1, U2.16 (VCC), U3.16 (VCC), U6.8 (VDD), U6.9 (I2C/~SPI), U7.8 (VDD), U7.9 (I2C/~SPI), U7.10 (A0/~CS), U10.2 (VO), X1.1 (EN), X1.4 (Vdd)
BATT_RAW: C1.1, C2.1, J2.1, U10.3 (VI)
GND: C1.2, C2.2, C3.2, C4.2, C5.2, C6.2, C10.2, C11.2, C15.2, J2.2, J10.4, J10.5, J10.SH, J11.4, J11.5, J11.SH, J12.4, J12.5, J12.SH, J13.4, J13.5, J13.SH, U2.15 (GND), U3.15 (GND), U6.2 (~CTSA), U6.10 (A0/~CS), U6.11 (A1/SI), U6.16 (~CTSB), U6.22 (VSS), U7.2 (~CTSA), U7.11 (A1/SI), U7.16 (~CTSB), U7.22 (VSS), U10.1 (GND), X1.2 (GND)
I2C_SCL: J1.2, R2.2, U6.13 (SCL/SCLK), U7.13 (SCL/SCLK)
I2C_SDA: J1.1, R1.2, U6.14 (SDA/VSS), U7.14 (SDA/VSS)
IRQ_SHARED: J1.3, R3.2, U6.15 (~IRQ), U7.15 (~IRQ)
J10_RXD: J10.6, R6.2
J10_TXD: J10.3, R5.2
J11_RXD: J11.6, R8.2
J11_TXD: J11.3, R7.2
J12_RXD: J12.6, R10.2
J12_TXD: J12.3, R9.2
J13_RXD: J13.6, R12.2
J13_TXD: J13.3, R11.2
OSC_CLK: U6.6 (XTAL1), U7.6 (XTAL1), X1.3 (OUT)
SC_RESET_SHARED: C5.1, R4.2, U6.5 (~RESET), U7.5 (~RESET)
U2_CPN: C7.2, U2.3 (C1-)
U2_CPN2: C8.2, U2.5 (C2-)
U2_CPP: C7.1, U2.1 (C1+)
U2_CPP2: C8.1, U2.4 (C2+)
U2_RX232A: R6.1, U2.13 (R1IN)
U2_RX232B: R8.1, U2.8 (R2IN)
U2_TX232A: R5.1, U2.14 (T1OUT)
U2_TX232B: R7.1, U2.7 (T2OUT)
U2_VSN: C9.2, U2.6 (VS-)
U2_VSP: C9.1, U2.2 (VS+)
U3_CPN: C12.2, U3.3 (C1-)
U3_CPN2: C13.2, U3.5 (C2-)
U3_CPP: C12.1, U3.1 (C1+)
U3_CPP2: C13.1, U3.4 (C2+)
U3_RX232A: R10.1, U3.13 (R1IN)
U3_RX232B: R12.1, U3.8 (R2IN)
U3_TX232A: R9.1, U3.14 (T1OUT)
U3_TX232B: R11.1, U3.7 (T2OUT)
U3_VSN: C14.2, U3.6 (VS-)
U3_VSP: C14.1, U3.2 (VS+)
U6_RXA: U2.12 (R1OUT), U6.4 (RXA)
U6_RXB: U2.9 (R2OUT), U6.24 (RXB)
U6_TXA: U2.11 (T1IN), U6.3 (TXA)
U6_TXB: U2.10 (T2IN), U6.23 (TXB)
U7_RXA: U3.12 (R1OUT), U7.4 (RXA)
U7_RXB: U3.9 (R2OUT), U7.24 (RXB)
U7_TXA: U3.11 (T1IN), U7.3 (TXA)
U7_TXB: U3.10 (T2IN), U7.23 (TXB)

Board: 2 copper layers, 39 parts (0 on the bottom side), 44 nets, no tracks yet.
